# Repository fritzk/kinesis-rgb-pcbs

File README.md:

# PCBs to add per-key RGB lighting to Kinesis Advantage

# Attribution

Board outlines and starting schematics:

* [Pillz Mod](https://github.com/dcpedit/pillzmod) for main and thumb pcbs
* [kinesis-fn](https://github.com/bluelightning32/kinesis-fn) for function key pcbs

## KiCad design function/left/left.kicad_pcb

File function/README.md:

imported from https://github.com/bluelightning32/kinesis-fn

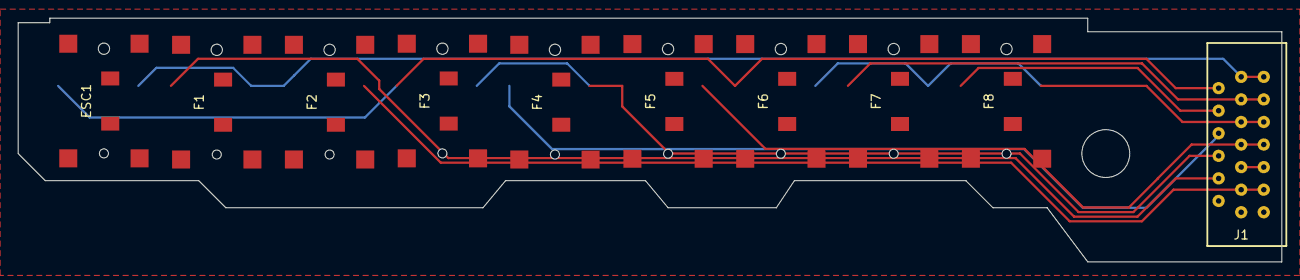
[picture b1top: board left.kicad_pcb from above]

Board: 2 copper layers, 140.0 x 27.0 mm, 11 parts (0 on the bottom side), 12 nets.

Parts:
ESC1: PG1316M; SW_PG1316M
F1, F2, F3, F4, F5, F6, F7, F8: PG1316M; SW_PG1316M
H1: MountingHole_5.3mm_M5
J1: FFC_Connector_13P

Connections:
GND: J1.1, J1.1B
unnamed: ESC1.1, F3.1, F6.1, J1.12
unnamed: ESC1.2, F1.2, F2.1, J1.13, J1.13B
unnamed: F1.1, J1.4
unnamed: F2.2, J1.3, J1.3B
unnamed: F3.2, F4.2, F5.1, J1.6
unnamed: F4.1, J1.8
unnamed: F5.2, J1.7, J1.7B
unnamed: F6.2, F7.2, F8.2, J1.9, J1.9B
unnamed: F7.1, J1.11, J1.11B
unnamed: F8.1, J1.10
unnamed: J1.5, J1.5B

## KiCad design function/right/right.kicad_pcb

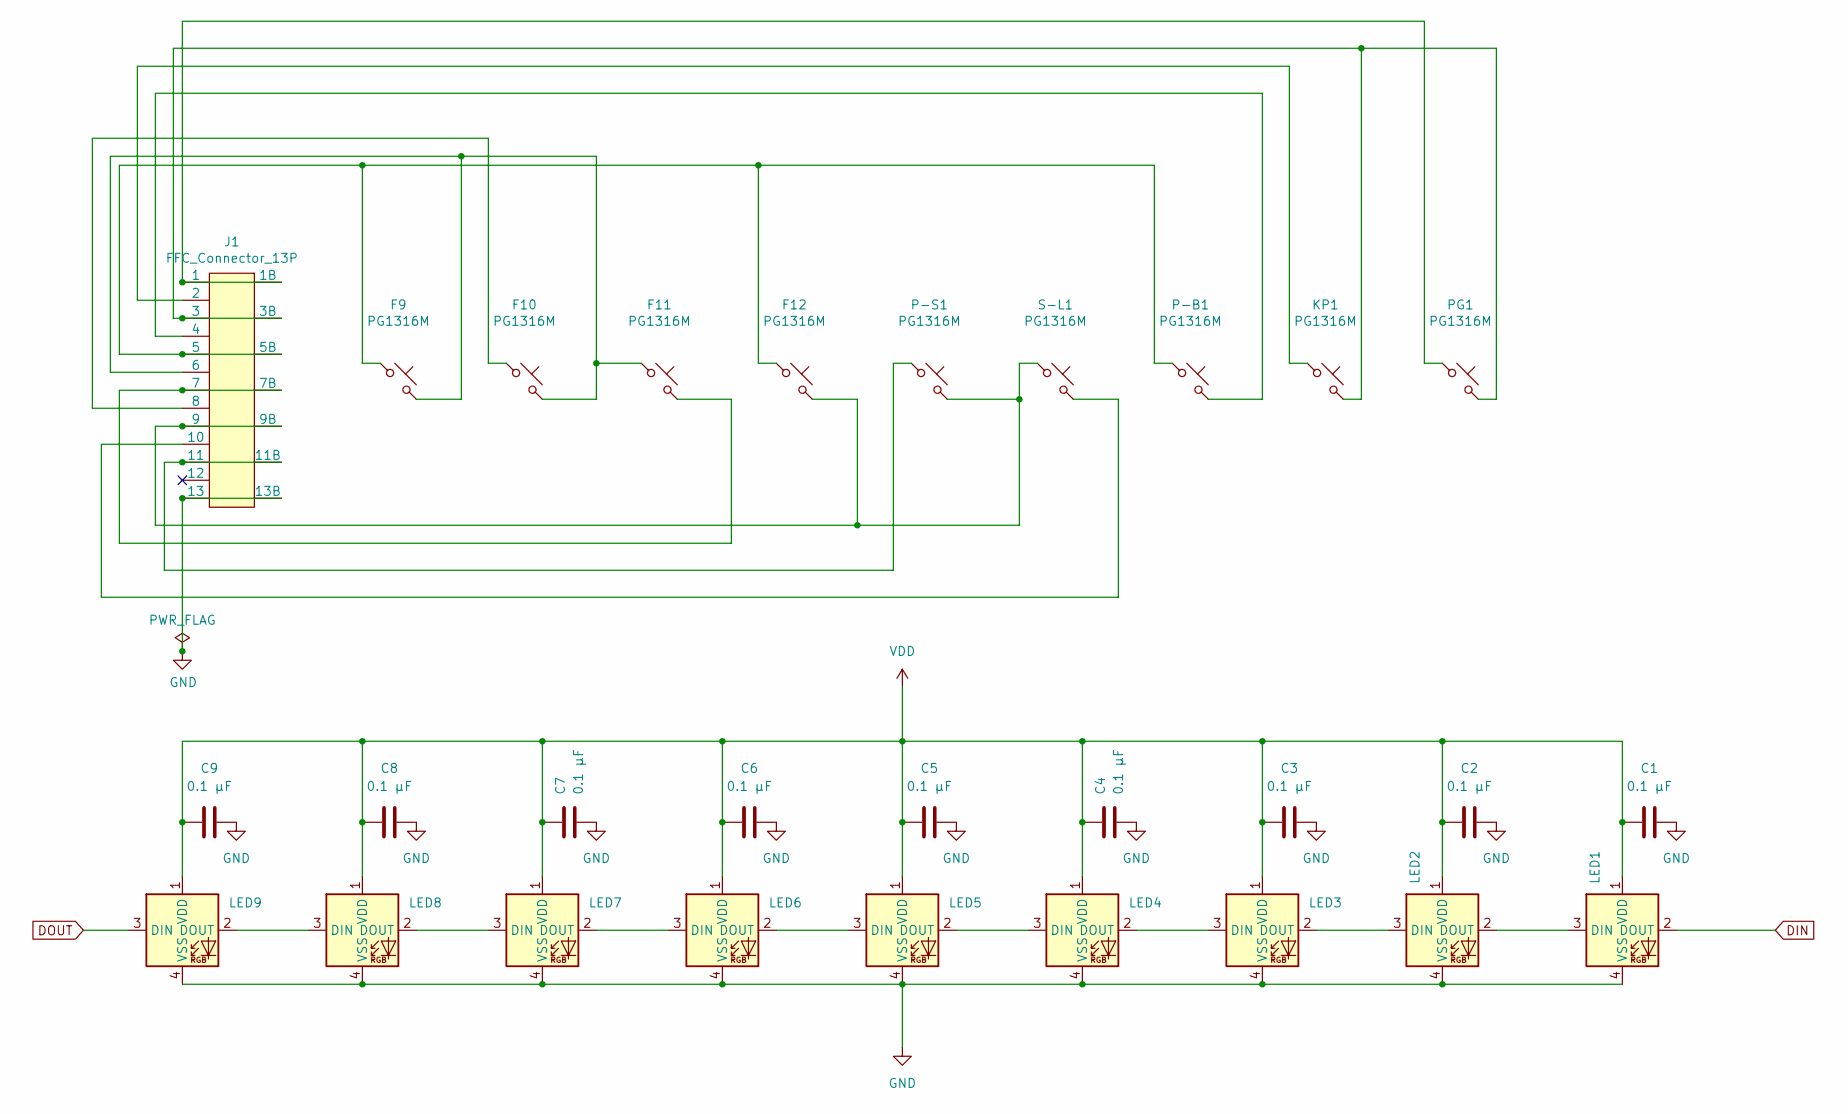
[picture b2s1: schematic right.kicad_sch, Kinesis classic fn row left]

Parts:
C1, C2, C3, C4, C5, C6, C7, C8, C9: 0.1 µF; C_0805_2012Metric_Pad1.18x1.45mm_HandSolder
F9, F10, F11, F12: PG1316M; SW_PG1316M
J1: FFC_Connector_13P
KP1: PG1316M; SW_PG1316M
LED1, LED2, LED3, LED4, LED5, LED6, LED7, LED8, LED9: MX_SK6812MINI-E; SK6812-MINI-E
P-B1: PG1316M; SW_PG1316M
P-S1: PG1316M; SW_PG1316M
PG1: PG1316M; SW_PG1316M
S-L1: PG1316M; SW_PG1316M

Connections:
DIN: LED1.2 (DOUT)
DOUT: LED9.3 (DIN)
GND: C1.2, C2.2, C3.2, C4.2, C5.2, C6.2, C7.2, C8.2, C9.2, J1.13, J1.13B, LED1.4 (VSS), LED2.4 (VSS), LED3.4 (VSS), LED4.4 (VSS), LED5.4 (VSS), LED6.4 (VSS), LED7.4 (VSS), LED8.4 (VSS), LED9.4 (VSS)
unnamed: F10.1, J1.8
unnamed: F9.2, F10.2, F11.1, J1.6
unnamed: F11.2, J1.7, J1.7B
unnamed: F9.1, F12.1, J1.5, J1.5B, P-B1.1
unnamed: F12.2, J1.9, J1.9B, P-S1.2, S-L1.1
unnamed: J1.1, J1.1B, PG1.1
unnamed: J1.2, KP1.1
unnamed: J1.3, J1.3B, KP1.2, PG1.2
unnamed: J1.4, P-B1.2
unnamed: J1.10, S-L1.2
unnamed: J1.11, J1.11B, P-S1.1
unnamed: LED1.3 (DIN), LED2.2 (DOUT)
unnamed: LED2.3 (DIN), LED3.2 (DOUT)
unnamed: LED3.3 (DIN), LED4.2 (DOUT)
unnamed: LED4.3 (DIN), LED5.2 (DOUT)
unnamed: LED5.3 (DIN), LED6.2 (DOUT)
unnamed: LED6.3 (DIN), LED7.2 (DOUT)
unnamed: LED7.3 (DIN), LED8.2 (DOUT)
unnamed: LED8.3 (DIN), LED9.2 (DOUT)
VDD: C1.1, C2.1, C3.1, C4.1, C5.1, C6.1, C7.1, C8.1, C9.1, LED1.1 (VDD), LED2.1 (VDD), LED3.1 (VDD), LED4.1 (VDD), LED5.1 (VDD), LED6.1 (VDD), LED7.1 (VDD), LED8.1 (VDD), LED9.1 (VDD)

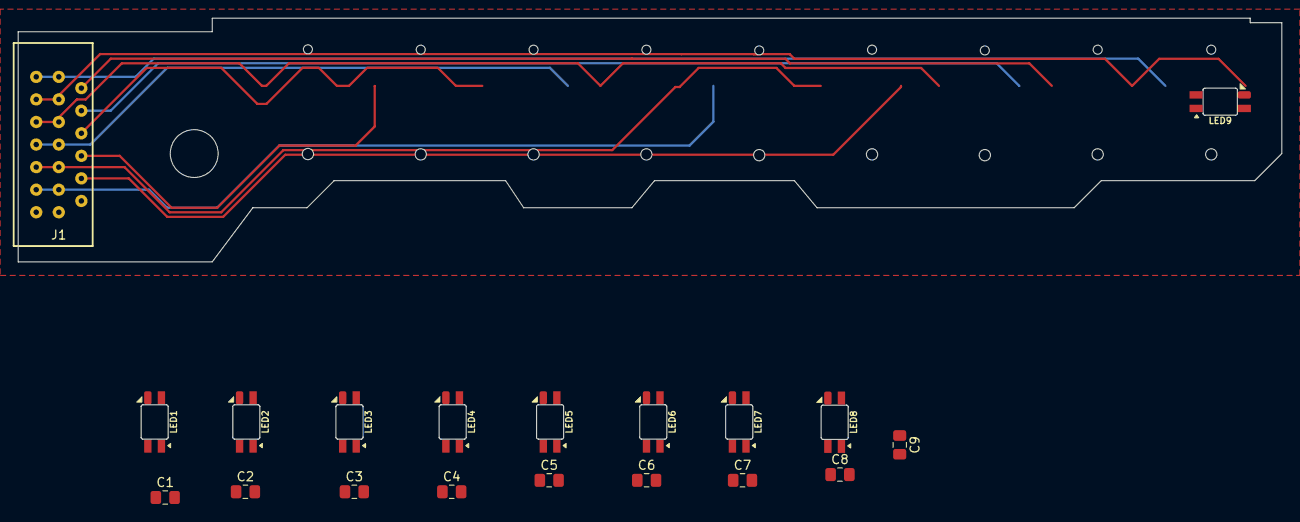
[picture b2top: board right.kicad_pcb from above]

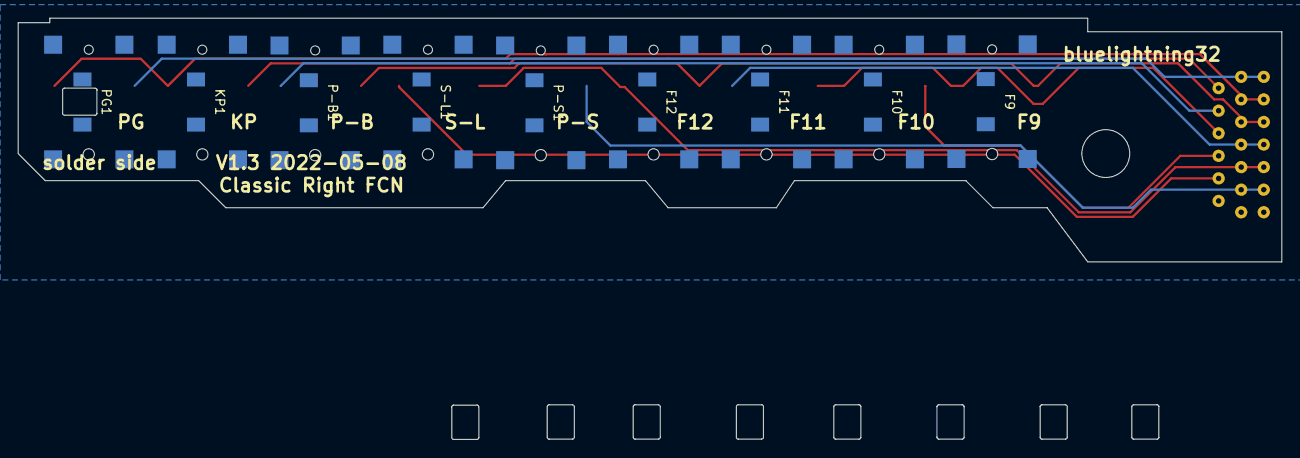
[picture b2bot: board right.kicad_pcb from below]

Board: 2 copper layers, 139.9 x 46.6 mm, 29 parts (9 on the bottom side), 21 nets.

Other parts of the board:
H1: MountingHole_5.3mm_M5

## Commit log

2026-05-25 import kinesis function keys
    from https://github.com/bluelightning32/kinesis-fn
2026-05-25 cleanup import
2026-05-25 drop -pcb from directory names
2026-05-25 finished images
2026-05-25 rgb switches
    convert to KiCad 9 (move directories)
    pg1316m switches
    sk6812mini-e lights
2026-05-25 drop Pillz Mod thumb cluster
    was used as reference
2026-05-25 add attribution

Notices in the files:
function/left/left.kicad_pcb:
License: MIT
function/right/right.kicad_sch:
MIT license
